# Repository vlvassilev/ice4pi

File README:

ice4pi-bridge is an open hardware platform for FPGA
development published by Lightside Instruments AS.

Based on ice4pi-2.0 board but with SMD instead of through-hole
2x20 pin connector and added additional dedicated set of IO pins
controling the extension side of the Pi interface.

The initial release ice4pi-bridge-1.0 includes schematic and PCB
design files for KiCAD.

The project is published by Lightside Instruments AS
under TAPR Open Hardware License. Read the LICENSE file
for details.

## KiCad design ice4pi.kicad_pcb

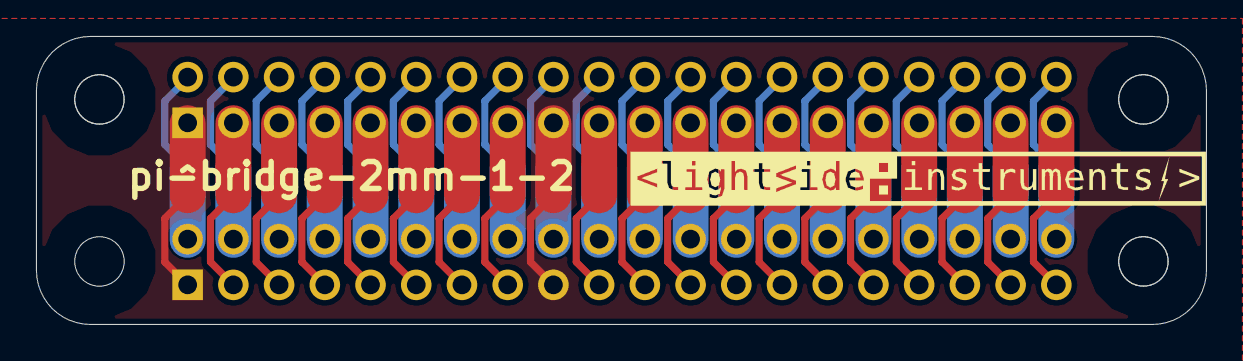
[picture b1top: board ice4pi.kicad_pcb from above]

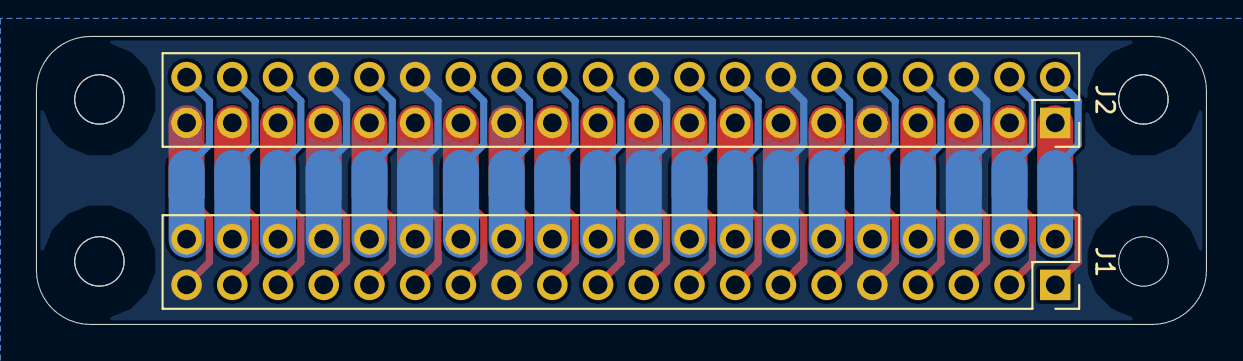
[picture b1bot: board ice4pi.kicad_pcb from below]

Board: 4 copper layers, 65.0 x 16.0 mm, 3 parts (2 on the bottom side), 31 nets.

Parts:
J1, J2: Conn_02x20_Odd_Even; PinSocket_2x20_P2.54mm_Vertical_1_04mm
svg2mod: G***; lsi-logo-32mm

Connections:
+3V3: J1.1, J1.17, J2.1, J2.17
+5V: J1.2, J1.4, J2.2, J2.4
GND: J1.6, J1.9, J1.14, J1.20, J1.25, J1.30, J1.34, J1.39, J2.6, J2.9, J2.14, J2.20, J2.25, J2.30, J2.34, J2.39
unnamed: J1.3, J2.3
unnamed: J1.5, J2.5
unnamed: J1.7, J2.7
unnamed: J1.8, J2.8
unnamed: J1.10, J2.10
unnamed: J1.11, J2.11
unnamed: J1.12, J2.12
unnamed: J1.13, J2.13
unnamed: J1.15, J2.15
unnamed: J1.16, J2.16
unnamed: J1.18, J2.18
unnamed: J1.19, J2.19
unnamed: J1.21, J2.21
unnamed: J1.22, J2.22
unnamed: J1.23, J2.23
unnamed: J1.24, J2.24
unnamed: J1.26, J2.26
unnamed: J1.27, J2.27
unnamed: J1.28, J2.28
unnamed: J1.29, J2.29
unnamed: J1.31, J2.31
unnamed: J1.32, J2.32
unnamed: J1.33, J2.33
unnamed: J1.35, J2.35
unnamed: J1.36, J2.36
unnamed: J1.37, J2.37
unnamed: J1.38, J2.38
unnamed: J1.40, J2.40

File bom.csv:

Reference,Quantity,Identifier,footprint,Value,Tolerance,Voltage,Current,Power,PN
J1,1,,ice4pi:PinSocket_2x20_P2.54mm_Vertical_1_04mm,-,,,,,2223
J2,1,,ice4pi:PinSocket_2x20_P2.54mm_Vertical_1_04mm,-,,,,,1992

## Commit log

2021-12-02 Release pi-bridge-1-1
2021-12-29 Release pi-bridge-2mm-1-1
2022-02-13 Release ice4pi-bridge-1.0
2022-02-13 Release pi-bridge-2mm-1-2
